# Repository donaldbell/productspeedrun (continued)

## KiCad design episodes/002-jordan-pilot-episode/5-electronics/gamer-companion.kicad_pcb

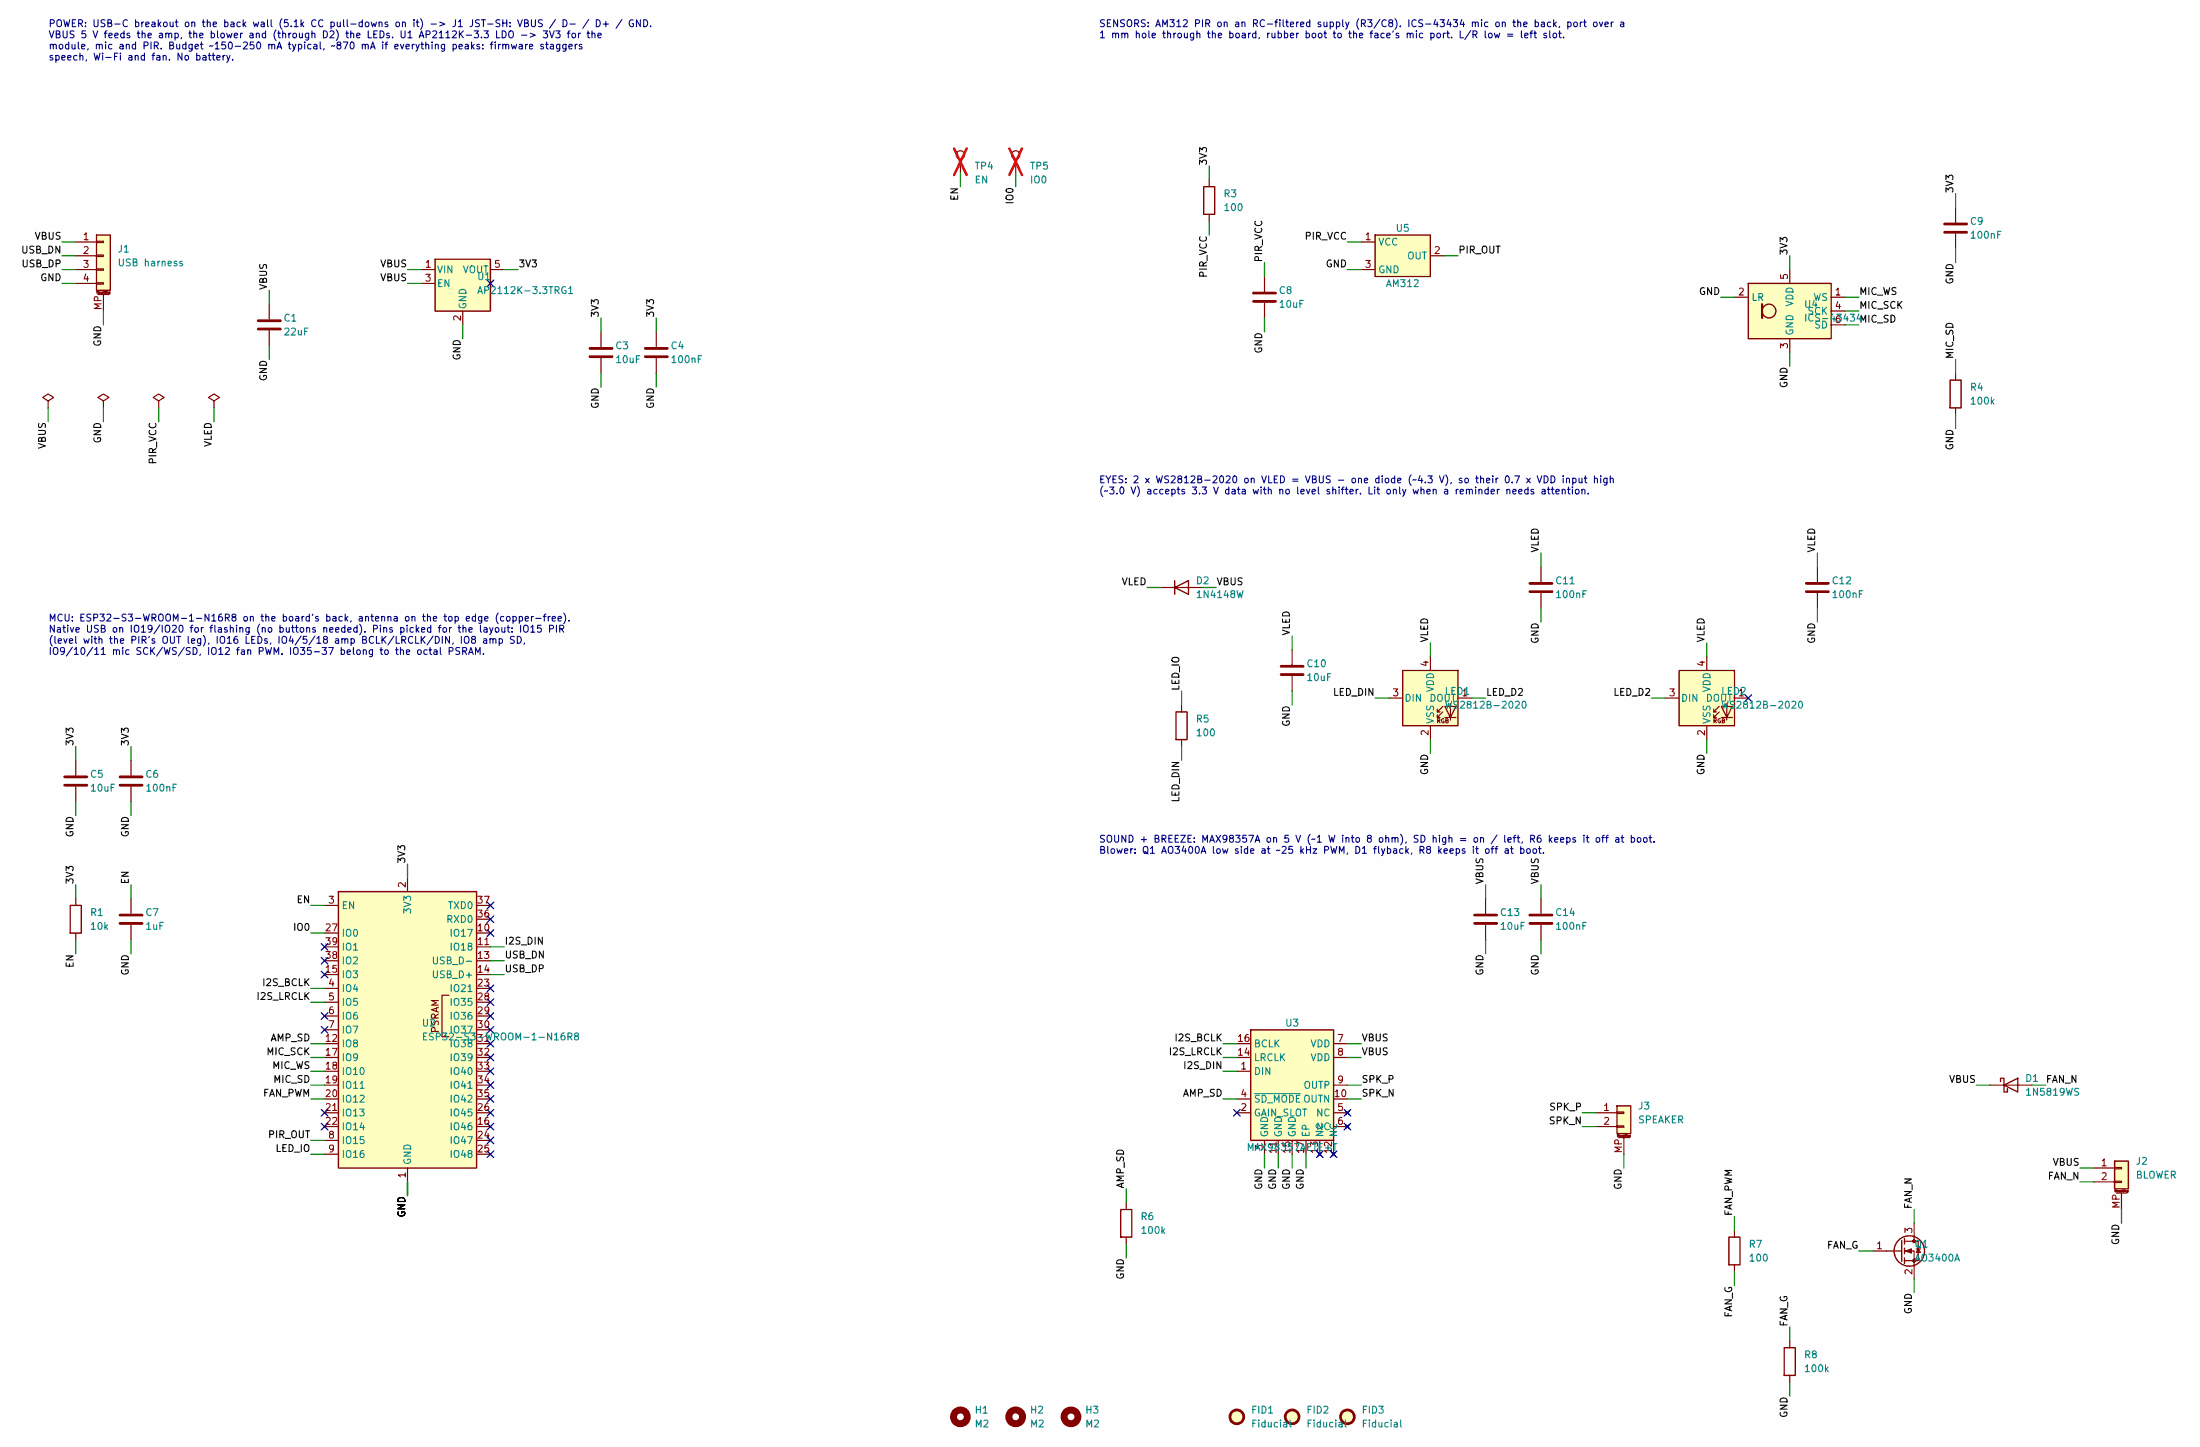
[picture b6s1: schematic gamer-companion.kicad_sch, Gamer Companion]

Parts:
C1: 22uF; C_0805_2012Metric; MPN CL21A226MAQNNNE; LCSC C45783
C3, C5, C8, C10, C13: 10uF; C_0805_2012Metric; MPN CL21A106KAYNNNE; LCSC C15850
C4, C6, C9, C11, C12, C14: 100nF; C_0603_1608Metric; MPN CC0603KRX7R9BB104; LCSC C14663
C7: 1uF; C_0603_1608Metric; MPN CL10A105KB8NNNC; LCSC C15849
D1: 1N5819WS; D_SOD-323; MPN 1N5819WS; LCSC C191023
D2: 1N4148W; D_SOD-123; MPN 1N4148W; LCSC C81598
FID1, FID2, FID3: Fiducial; Fiducial_1mm_Mask2mm
H1, H2, H3: M2; MountingHole_2.2mm_M2
J1: USB harness; JST_SH_SM04B-SRSS-TB_1x04-1MP_P1.00mm_Horizontal; MPN SM04B-SRSS-TB(LF)(SN); LCSC C160390
J2: BLOWER; JST_SH_SM02B-SRSS-TB_1x02-1MP_P1.00mm_Horizontal; MPN SM02B-SRSS-TB(LF)(SN); LCSC C160402
J3: SPEAKER; JST_SH_SM02B-SRSS-TB_1x02-1MP_P1.00mm_Horizontal; MPN SM02B-SRSS-TB(LF)(SN); LCSC C160402
LED1, LED2: WS2812B-2020; LED_WS2812B-2020_PLCC4_2.0x2.0mm; MPN WS2812B-2020; LCSC C965555
Q1: AO3400A; SOT-23; MPN AO3400A; LCSC C20917
R1: 10k; R_0603_1608Metric; MPN 0603WAF1002T5E; LCSC C25804
R3, R5, R7: 100; R_0603_1608Metric; MPN 0603WAF1000T5E; LCSC C22775
R4, R6, R8: 100k; R_0603_1608Metric; MPN 0603WAF1003T5E; LCSC C25803
TP4: EN; TestPoint_Pad_D1.5mm; not fitted
TP5: IO0; TestPoint_Pad_D1.5mm; not fitted
U1: AP2112K-3.3TRG1; SOT-23-5; MPN AP2112K-3.3TRG1; LCSC C51118
U2: ESP32-S3-WROOM-1-N16R8; ESP32-S3-WROOM-1; MPN ESP32-S3-WROOM-1-N16R8; LCSC C2913202
U3: MAX98357AETE+T; TQFN-16-1EP_3x3mm_P0.5mm_EP1.23x1.23mm_ThermalVias; MPN MAX98357AETE+T
U4: ICS-43434; InvenSense_ICS-43434-6_3.5x2.65mm; MPN ICS-43434
U5: AM312; PinHeader_1x03_P2.54mm_Vertical; MPN AM312

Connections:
/3V3: C3.1, C4.1, C5.1, C6.1, C9.1, R1.1, R3.1, U1.5 (VOUT), U2.2 (3V3), U4.5 (VDD)
/AMP_SD: R6.1, U2.12 (IO8), U3.4 (~SD_MODE)
/EN: C7.1, R1.2, TP4.1, U2.3 (EN)
/FAN_G: Q1.1 (G), R7.2, R8.1
/FAN_N: D1.2 (A), J2.2, Q1.3 (D)
/FAN_PWM: R7.1, U2.20 (IO12)
/GND: C1.2, C3.2, C4.2, C5.2, C6.2, C7.2, C8.2, C9.2, C10.2, C11.2, C12.2, C13.2, C14.2, J1.4, J1.MP (MountPin), J2.MP (MountPin), J3.MP (MountPin), LED1.2 (VSS), LED2.2 (VSS), Q1.2 (S), R4.2, R6.2, R8.2, U1.2 (GND), U2.1 (GND), U2.40 (GND), U2.41 (GND), U3.3 (GND), U3.11 (GND), U3.15 (GND), U3.17 (EP), U4.2 (LR), U4.3 (GND), U5.3 (GND)
/I2S_BCLK: U2.4 (IO4), U3.16 (BCLK)
/I2S_DIN: U2.11 (IO18), U3.1 (DIN)
/I2S_LRCLK: U2.5 (IO5), U3.14 (LRCLK)
/IO0: TP5.1, U2.27 (IO0)
/LED_D2: LED1.1 (DOUT), LED2.3 (DIN)
/LED_DIN: LED1.3 (DIN), R5.2
/LED_IO: R5.1, U2.9 (IO16)
/MIC_SCK: U2.17 (IO9), U4.4 (SCK)
/MIC_SD: R4.1, U2.19 (IO11), U4.6 (SD)
/MIC_WS: U2.18 (IO10), U4.1 (WS)
/PIR_OUT: U2.8 (IO15), U5.2 (OUT)
/PIR_VCC: C8.1, R3.2, U5.1 (VCC)
/SPK_N: J3.2, U3.10 (OUTN)
/SPK_P: J3.1, U3.9 (OUTP)
/USB_DN: J1.2, U2.13 (USB_D-)
/USB_DP: J1.3, U2.14 (USB_D+)
/VBUS: C1.1, C13.1, C14.1, D1.1 (K), D2.2 (A), J1.1, J2.1, U1.1 (VIN), U1.3 (EN), U3.7 (VDD), U3.8 (VDD)
/VLED: C10.1, C11.1, C12.1, D2.1 (K), LED1.4 (VDD), LED2.4 (VDD)

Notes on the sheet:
POWER: USB-C breakout on the back wall (5.1k CC pull-downs on it) -> J1 JST-SH: VBUS / D- / D+ / GND. VBUS 5 V feeds the amp, the blower and (through D2) the LEDs. U1 AP2112K-3.3 LDO -> 3V3 for the module, mic and PIR. Budget ~150-250 mA typical, ~870 mA if everything peaks: firmware staggers speec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
MCU: ESP32-S3-WROOM-1-N16R8 on the board's back, antenna on the top edge (copper-free). Native USB on IO19/IO20 for flashing (no buttons needed). Pins picked for the layout: IO15 PIR (level with the PIR's OUT leg), IO16 LEDs, IO4/5/18 amp BCLK/LRCLK/DIN, IO8 amp SD, IO9/10/11 mic SCK/WS/SD, IO12 fa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
SENSORS: AM312 PIR on an RC-filtered supply (R3/C8). ICS-43434 mic on the back, port over a 1 mm hole through the board, rubber boot to the face's mic port. L/R low = left slot.
EYES: 2 x WS2812B-2020 on VLED = VBUS - one diode (~4.3 V), so their 0.7 x VDD input high (~3.0 V) accepts 3.3 V data with no level shifter. Lit only when a reminder needs attention.
SOUND + BREEZE: MAX98357A on 5 V (~1 W into 8 ohm), SD high = on / left, R6 keeps it off at boot. Blower: Q1 AO3400A low side at ~25 kHz PWM, D1 flyback, R8 keeps it off at boot.

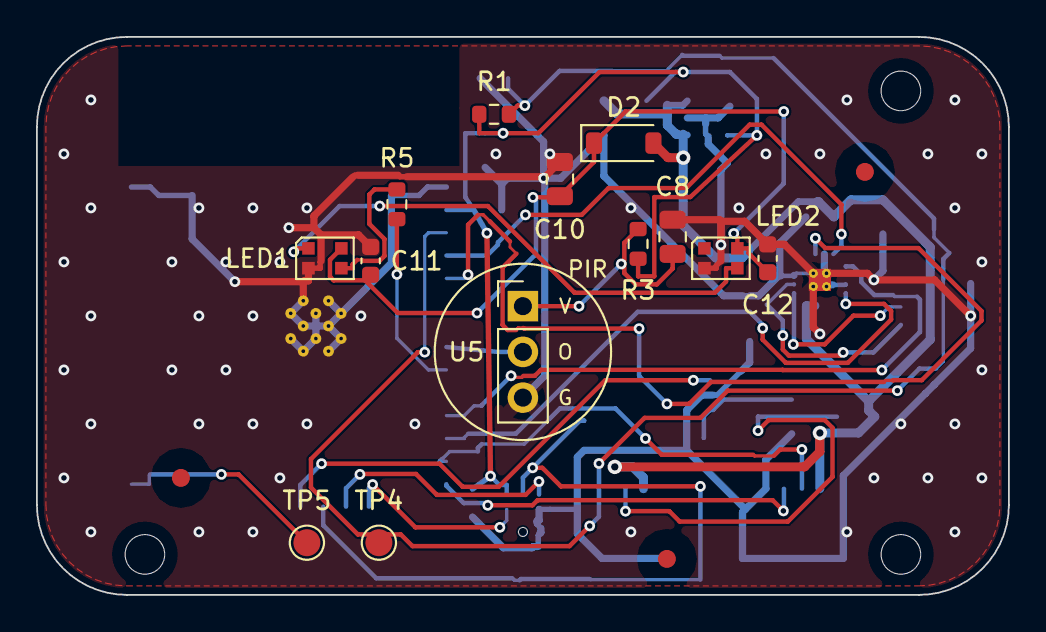
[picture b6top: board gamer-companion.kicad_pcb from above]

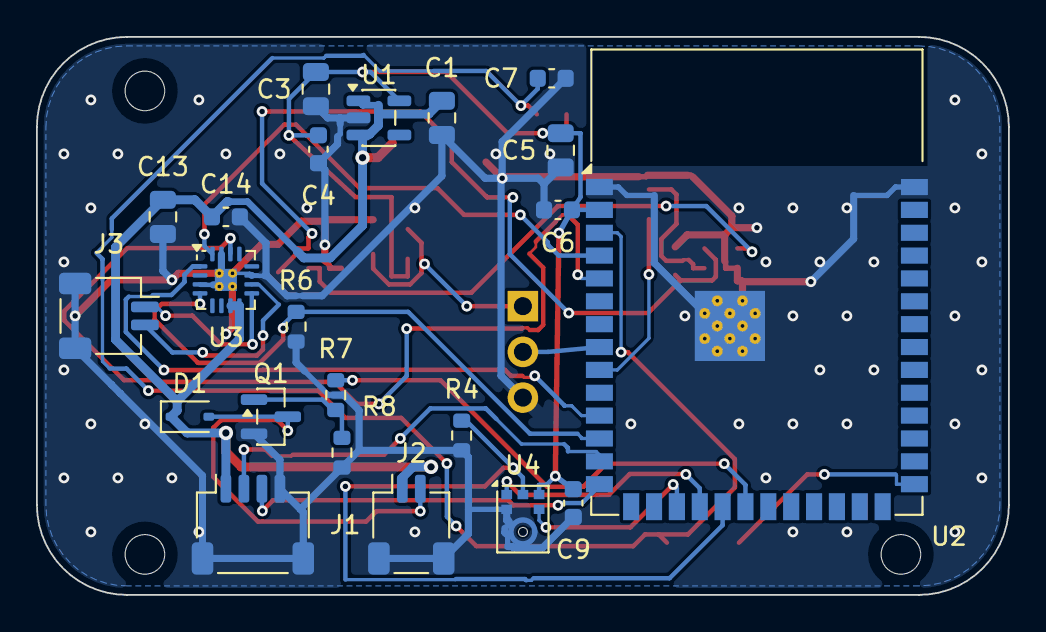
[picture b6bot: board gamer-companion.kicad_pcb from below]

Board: 2 copper layers, 54.0 x 31.0 mm, 41 parts (22 on the bottom side), 25 nets.

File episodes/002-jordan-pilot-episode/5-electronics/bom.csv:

Ref,Qty,Value,Description,Footprint,MPN
C1,1,22uF,"Capacitor, ceramic, 22 uF 25 V X5R 0805",C_0805_2012Metric,CL21A226MAQNNNE
C2 C3 C5 C8 C10 C13,6,10uF,"Capacitor, ceramic, 10 uF 25 V X5R 0805",C_0805_2012Metric,CL21A106KAYNNNE
C4 C6 C9 C11 C12 C14,6,100nF,"Capacitor, ceramic, 100 nF 50 V X7R 0603",C_0603_1608Metric,CC0603KRX7R9BB104
C7,1,1uF,"Capacitor, ceramic, 1 uF 50 V X5R 0603",C_0603_1608Metric,CL10A105KB8NNNC
D1,1,1N5819WS,Schottky 40 V 1 A SOD-323: flyback across the blower,D_SOD-323,1N5819WS
D2,1,1N4148W,"Signal diode, SOD-123: drops VBUS to ~4.3 V so 3.3 V data reads as high",D_SOD-123,1N4148W
J1,1,USB harness,JST-SH 4-pin: VBUS / D- / D+ / GND from the USB-C breakout on the back wall (it carries the 5.1k CC pull-downs),JST_SH_SM04B-SRSS-TB_1x04-1MP_P1.00mm_Horizontal,SM04B-SRSS-TB(LF)(SN)
J2,1,BLOWER,JST-SH 2-pin to the 5 V 3010 blower (+ on pin 1),JST_SH_SM02B-SRSS-TB_1x02-1MP_P1.00mm_Horizontal,SM02B-SRSS-TB(LF)(SN)
J3,1,SPEAKER,JST-SH 2-pin to the 28 mm 8 ohm speaker on the right wall,JST_SH_SM02B-SRSS-TB_1x02-1MP_P1.00mm_Horizontal,SM02B-SRSS-TB(LF)(SN)
LED1 LED2,2,WS2812B-2020,"RGB LED 2 x 2 mm, left eye",LED_WS2812B-2020_PLCC4_2.0x2.0mm,WS2812B-2020
Q1,1,AO3400A,N-MOSFET 30 V 5.7 A SOT-23: low-side PWM switch for the blower,SOT-23,AO3400A
R1 R2,2,10k,"Resistor, 1 %, 0603, 10k",R_0603_1608Metric,0603WAF1002T5E
R3 R5 R7,3,100,"Resistor, 1 %, 0603, 100",R_0603_1608Metric,0603WAF1000T5E
R4 R6 R8,3,100k,"Resistor, 1 %, 0603, 100k",R_0603_1608Metric,0603WAF1003T5E
U1,1,AP2112K-3.3TRG1,"LDO 3.3 V 600 mA, SOT-23-5, EN tied to VIN (always on)",SOT-23-5,AP2112K-3.3TRG1
U2,1,ESP32-S3-WROOM-1-N16R8,"ESP32-S3 Wi-Fi/BLE module, 16 MB flash + 8 MB octal PSRAM (runs ESP-SR on-device), PCB antenna, 18 x 25.5 x 3.1 mm",ESP32-S3-WROOM-1,ESP32-S3-WROOM-1-N16R8
U3,1,MAX98357AETE+T,"I2S class-D mono amplifier on 5 V, TQFN-16 3 x 3 mm",TQFN-16-1EP_3x3mm_P0.5mm_EP1.23x1.23mm_ThermalVias,MAX98357AETE+T
U4,1,ICS-43434,"I2S MEMS microphone, bottom port (over a 1 mm hole in the board), L/R low = left slot",InvenSense_ICS-43434-6_3.5x2.65mm,ICS-43434
U5,1,AM312,Mini PIR motion sensor; dome through the visor,PinHeader_1x03_P2.54mm_Vertical,AM312
BLOWER,1,3010 blower 5 V,"Radial blower 30 x 30 x 10 mm, 5 V ~150 mA, lead re-terminated to JST-SH (J2)",off-board,generic 3010 5 V blower
LS1,1,8 ohm 1 W,"Speaker 28 mm round, 8 ohm 1 W, ~5 mm thick, on the right wall behind the grille (J3)",off-board,generic 28 mm 8 ohm 1 W
USB-C,1,USB-C breakout,"USB-C receptacle breakout with VBUS/D+/D-/GND and 5.1k CC pull-downs, on the back wall (J1)",off-board,generic 4-wire USB-C breakout

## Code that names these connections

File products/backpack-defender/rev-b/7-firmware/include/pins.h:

// GENERATED by scripts/gen_pins.py from ../5-electronics/src/design.py. Do not edit: change the board, then rebuild.
// Every PIN_* can be overridden with a build flag (-DPIN_RGB_DATA=8 for a plain ESP32-C3 dev board).
#pragma once

#define BOARD_NAME "Backpack Defender Rev B"

// PIR_OUT: to J4.2; can wake from deep sleep
#ifndef PIN_PIR_OUT
#define PIN_PIR_OUT 0
#endif
#define PIN_PIR_OUT_PULLUP 0
#define PIN_PIR_OUT_PULLDOWN 0

// BTN: pull-up R9 100k; to SW1.1; can wake from deep sleep
#ifndef PIN_BTN
#define PIN_BTN 1
#endif
#define PIN_BTN_PULLUP 1
#define PIN_BTN_PULLDOWN 0

// IO2: pull-up R6 10k; strapping pin; can wake from deep sleep
#ifndef PIN_IO2
#define PIN_IO2 2
#endif
#define PIN_IO2_PULLUP 1
#define PIN_IO2_PULLDOWN 0

// VBAT_SENSE: pull-down R4 1M; to C4.1, R3.2; can wake from deep sleep
#ifndef PIN_VBAT_SENSE
#define PIN_VBAT_SENSE 3
#endif
#define PIN_VBAT_SENSE_PULLUP 0
#define PIN_VBAT_SENSE_PULLDOWN 1

// I2S_BCLK: to U3.16; can wake from deep sleep
#ifndef PIN_I2S_BCLK
#define PIN_I2S_BCLK 4
#endif
#define PIN_I2S_BCLK_PULLUP 0
#define PIN_I2S_BCLK_PULLDOWN 0

// I2S_LRCLK: to U3.14; can wake from deep sleep
#ifndef PIN_I2S_LRCLK
#define PIN_I2S_LRCLK 5
#endif
#define PIN_I2S_LRCLK_PULLUP 0
#define PIN_I2S_LRCLK_PULLDOWN 0

// I2S_DIN: to U3.1
#ifndef PIN_I2S_DIN
#define PIN_I2S_DIN 6
#endif
#define PIN_I2S_DIN_PULLUP 0
#define PIN_I2S_DIN_PULLDOWN 0

// AMP_SD: pull-down R11 100k; to U3.4
#ifndef PIN_AMP_SD
#define PIN_AMP_SD 7
#endif
#define PIN_AMP_SD_PULLUP 0
#define PIN_AMP_SD_PULLDOWN 1

// IO8: pull-up R7 10k; strapping pin
#ifndef PIN_IO8
#define PIN_IO8 8
#endif
#define PIN_IO8_PULLUP 1
#define PIN_IO8_PULLDOWN 0

// IO9: pull-up R8 10k; to J2.6; strapping pin
#ifndef PIN_IO9
#define PIN_IO9 9
#endif
#define PIN_IO9_PULLUP 1
#define PIN_IO9_PULLDOWN 0

// EYE_LED: pull-down R16 100k; to Q2.1
#ifndef PIN_EYE_LED
#define PIN_EYE_LED 10
#endif
#define PIN_EYE_LED_PULLUP 0
#define PIN_EYE_LED_PULLDOWN 1

// USB_DN: to J2.3
#ifndef PIN_USB_DN
#define PIN_USB_DN 18
#endif
#define PIN_USB_DN_PULLUP 0
#define PIN_USB_DN_PULLDOWN 0

// USB_DP: to J2.4
#ifndef PIN_USB_DP
#define PIN_USB_DP 19
#endif
#define PIN_USB_DP_PULLUP 0
#define PIN_USB_DP_PULLDOWN 0

// RGB_DATA: to R18.1
#ifndef PIN_RGB_DATA
#define PIN_RGB_DATA 20
#endif
#define PIN_RGB_DATA_PULLUP 0
#define PIN_RGB_DATA_PULLDOWN 0

// RGB_PWR_N: pull-up R17 100k; to Q3.1
#ifndef PIN_RGB_PWR_N
#define PIN_RGB_PWR_N 21
#endif
#define PIN_RGB_PWR_N_PULLUP 1
#define PIN_RGB_PWR_N_PULLDOWN 0

// VBAT_SENSE = VBAT x 1e+06 / (1e+06 + 1e+06): multiply the pin voltage by this to get VBAT
#define VBAT_SENSE_RATIO 2.0000f

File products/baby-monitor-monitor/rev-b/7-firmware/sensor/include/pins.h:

// GENERATED by ../common/scripts/gen_pins.py from ../../5-electronics/sensor/src/design.py. Do not edit: change the board, then rebuild.
// pad table cross-checked against KiCad's ESP32-C6-MINI-1 symbol (U3, RF_Module:ESP32-C6-MINI-1).
// Every PIN_* can be overridden with a build flag (the devkit envs in platformio.ini do).
#pragma once

#define BOARD_NAME "Baby Monitor Monitor: Sensor"
#define BOARD_KEY "sensor"

// VBAT_SENSE: pull-down R6 1M; to C5.1, R5.2; LP GPIO (can wake from deep sleep); ADC1 ch0
#ifndef PIN_VBAT_SENSE
#define PIN_VBAT_SENSE 0
#endif
#define PIN_VBAT_SENSE_PULLUP 0
#define PIN_VBAT_SENSE_PULLDOWN 1

// MIC_SD: to U4.6; LP GPIO (can wake from deep sleep); ADC1 ch2
#ifndef PIN_MIC_SD
#define PIN_MIC_SD 2
#endif
#define PIN_MIC_SD_PULLUP 0
#define PIN_MIC_SD_PULLDOWN 0

// LED_IO: to R9.1; LP GPIO (can wake from deep sleep); ADC1 ch3
#ifndef PIN_LED_IO
#define PIN_LED_IO 3
#endif
#define PIN_LED_IO_PULLUP 0
#define PIN_LED_IO_PULLDOWN 0

// MIC_SCK: to U4.4; strapping pin; LP GPIO (can wake from deep sleep); ADC1 ch4
#ifndef PIN_MIC_SCK
#define PIN_MIC_SCK 4
#endif
#define PIN_MIC_SCK_PULLUP 0
#define PIN_MIC_SCK_PULLDOWN 0

// MIC_WS: to U4.1; strapping pin; LP GPIO (can wake from deep sleep); ADC1 ch5
#ifndef PIN_MIC_WS
#define PIN_MIC_WS 5
#endif
#define PIN_MIC_WS_PULLUP 0
#define PIN_MIC_WS_PULLDOWN 0

// BAR_IO: to R10.1; LP GPIO (can wake from deep sleep); ADC1 ch6
#ifndef PIN_BAR_IO
#define PIN_BAR_IO 6
#endif
#define PIN_BAR_IO_PULLUP 0
#define PIN_BAR_IO_PULLDOWN 0

// BTN: to SW1.1, SW3.1; LP GPIO (can wake from deep sleep)
#ifndef PIN_BTN
#define PIN_BTN 7
#endif
#define PIN_BTN_PULLUP 0
#define PIN_BTN_PULLDOWN 0

// IO8: pull-up R8 10k; strapping pin
#ifndef PIN_IO8
#define PIN_IO8 8
#endif
#define PIN_IO8_PULLUP 1
#define PIN_IO8_PULLDOWN 0

// IO9: to TP1.1; strapping pin
#ifndef PIN_IO9
#define PIN_IO9 9
#endif
#define PIN_IO9_PULLUP 0
#define PIN_IO9_PULLDOWN 0

// USB_DN: to J1.A7, J1.B7; native USB D-
#ifndef PIN_USB_DN
#define PIN_USB_DN 12
#endif
#define PIN_USB_DN_PULLUP 0
#define PIN_USB_DN_PULLDOWN 0

// USB_DP: to J1.A6, J1.B6; native USB D+
#ifndef PIN_USB_DP
#define PIN_USB_DP 13
#endif
#define PIN_USB_DP_PULLUP 0
#define PIN_USB_DP_PULLDOWN 0

// CHG_STAT: to U1.1
#ifndef PIN_CHG_STAT
#define PIN_CHG_STAT 21
#endif
#define PIN_CHG_STAT_PULLUP 0
#define PIN_CHG_STAT_PULLDOWN 0

// VBAT_SENSE = VBAT x 1e+06 / (1e+06 + 1e+06): multiply the pin voltage by this to get VBAT
#define VBAT_SENSE_RATIO 2.0000f

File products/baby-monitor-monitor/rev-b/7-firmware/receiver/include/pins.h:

// GENERATED by ../common/scripts/gen_pins.py from ../../5-electronics/receiver/src/design.py. Do not edit: change the board, then rebuild.
// pad table cross-checked against KiCad's ESP32-C6-MINI-1 symbol (U3, RF_Module:ESP32-C6-MINI-1).
// Every PIN_* can be overridden with a build flag (the devkit envs in platformio.ini do).
#pragma once

#define BOARD_NAME "Baby Monitor Monitor: Receiver"
#define BOARD_KEY "receiver"

// VBAT_SENSE: pull-down R3 1M; to C4.1, R2.2; LP GPIO (can wake from deep sleep); ADC1 ch0
#ifndef PIN_VBAT_SENSE
#define PIN_VBAT_SENSE 0
#endif
#define PIN_VBAT_SENSE_PULLUP 0
#define PIN_VBAT_SENSE_PULLDOWN 1

// CHG_STAT: to U1.1; LP GPIO (can wake from deep sleep); ADC1 ch1
#ifndef PIN_CHG_STAT
#define PIN_CHG_STAT 1
#endif
#define PIN_CHG_STAT_PULLUP 0
#define PIN_CHG_STAT_PULLDOWN 0

// MOT_PWM: pull-down R6 100k; to Q1.1; LP GPIO (can wake from deep sleep); ADC1 ch2
#ifndef PIN_MOT_PWM
#define PIN_MOT_PWM 2
#endif
#define PIN_MOT_PWM_PULLUP 0
#define PIN_MOT_PWM_PULLDOWN 1

// LED_IO: to LED1.3; LP GPIO (can wake from deep sleep); ADC1 ch6
#ifndef PIN_LED_IO
#define PIN_LED_IO 6
#endif
#define PIN_LED_IO_PULLUP 0
#define PIN_LED_IO_PULLDOWN 0

// LINK_IO: to R7.1; LP GPIO (can wake from deep sleep)
#ifndef PIN_LINK_IO
#define PIN_LINK_IO 7
#endif
#define PIN_LINK_IO_PULLUP 0
#define PIN_LINK_IO_PULLDOWN 0

// IO8: pull-up R5 10k; strapping pin
#ifndef PIN_IO8
#define PIN_IO8 8
#endif
#define PIN_IO8_PULLUP 1
#define PIN_IO8_PULLDOWN 0

// IO9: to TP1.1; strapping pin
#ifndef PIN_IO9
#define PIN_IO9 9
#endif
#define PIN_IO9_PULLUP 0
#define PIN_IO9_PULLDOWN 0

// USB_DN: to TP3.1; native USB D-
#ifndef PIN_USB_DN
#define PIN_USB_DN 12
#endif
#define PIN_USB_DN_PULLUP 0
#define PIN_USB_DN_PULLDOWN 0

// USB_DP: to TP2.1; native USB D+
#ifndef PIN_USB_DP
#define PIN_USB_DP 13
#endif
#define PIN_USB_DP_PULLUP 0
#define PIN_USB_DP_PULLDOWN 0

// VBAT_SENSE = VBAT x 1e+06 / (1e+06 + 1e+06): multiply the pin voltage by this to get VBAT
#define VBAT_SENSE_RATIO 2.0000f
